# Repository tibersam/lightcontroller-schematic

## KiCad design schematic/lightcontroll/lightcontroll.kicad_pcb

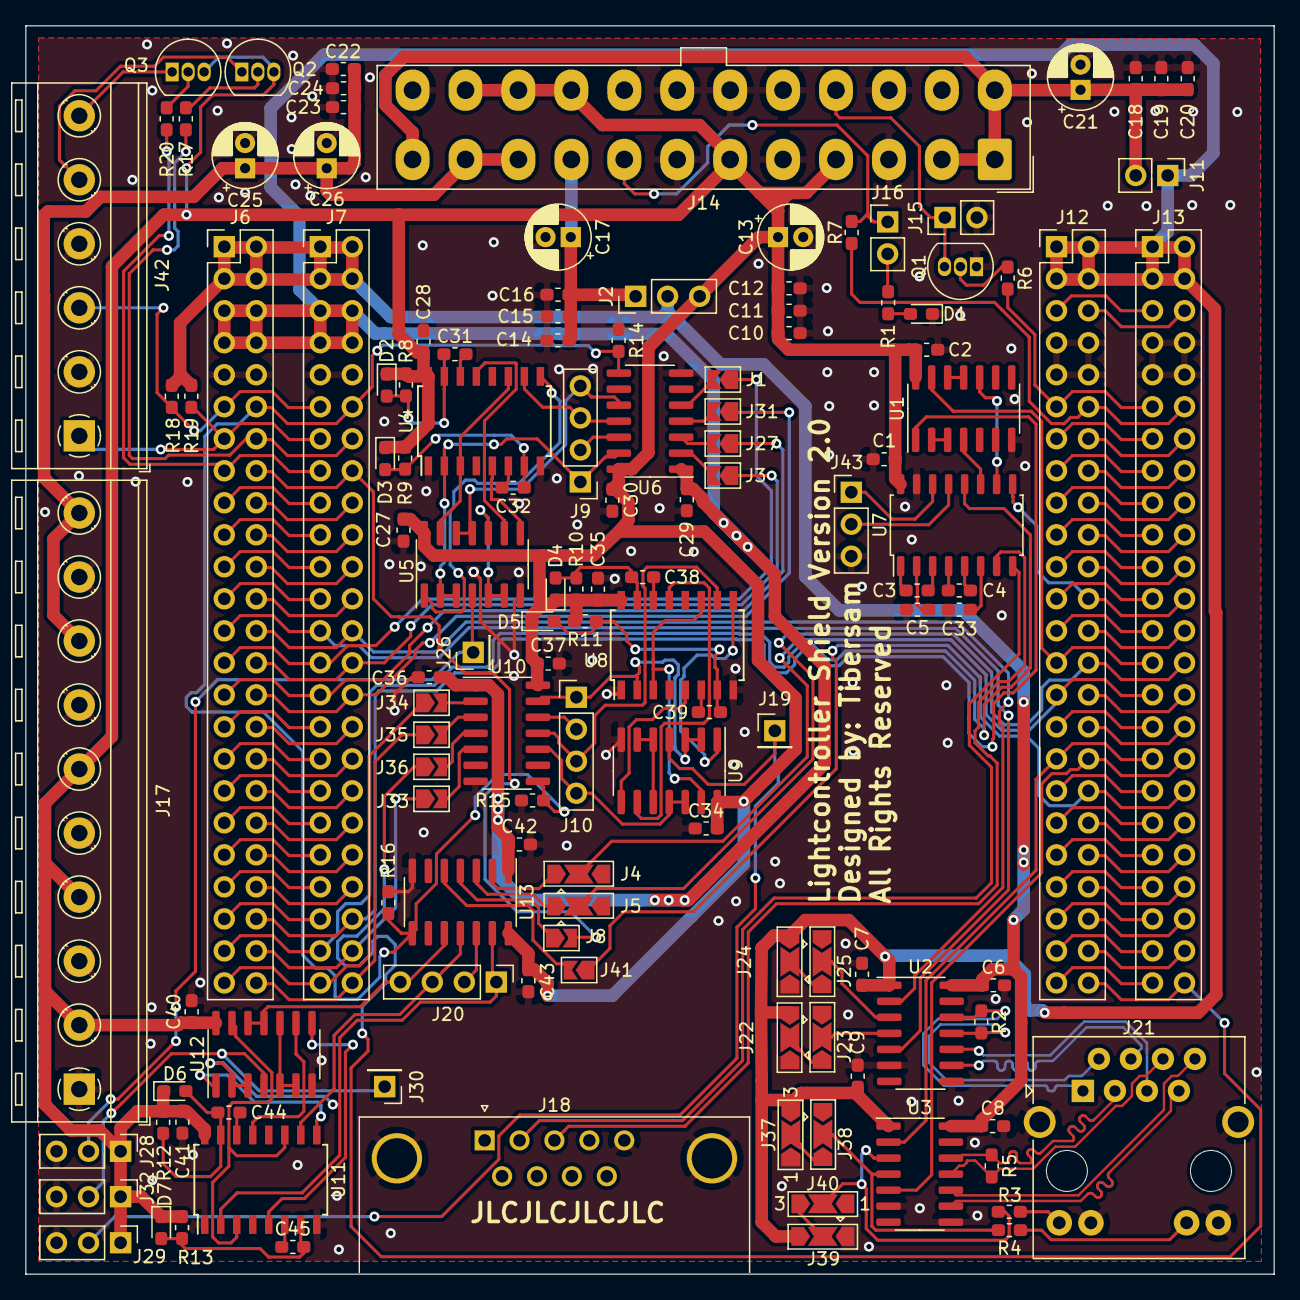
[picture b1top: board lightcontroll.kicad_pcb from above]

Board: 2 copper layers, 99.1 x 99.1 mm, 131 parts (0 on the bottom side), 180 nets.

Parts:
C1, C3, C4, C5, C6, C8, C11, C15, C19, C23, C33: 1uF; C_0603_1608Metric_Pad1.05x0.95mm_HandSolder
C2, C7, C9, C10, C14, C18, C22, C27, C28, C29, C30, C34, C35, C36, C37, C40, C41, C42, C43: 100nF; C_0603_1608Metric_Pad1.05x0.95mm_HandSolder
C12, C16, C20, C24: 10uF; C_0603_1608Metric_Pad1.05x0.95mm_HandSolder
C13, C17, C21, C25, C26: 100uF; CP_Radial_D5.0mm_P2.00mm
C31, C32, C38, C39, C44, C45: 200pF; C_0603_1608Metric_Pad1.05x0.95mm_HandSolder
D1: LED; LED_0603_1608Metric_Pad1.05x0.95mm_HandSolder
D2, D3, D4, D5, D6, D7: D_Schottky; D_0603_1608Metric_Pad1.05x0.95mm_HandSolder
J1: SPI1_SS; SolderJumper-2_P1.3mm_Open_TrianglePad1.0x1.5mm
J2: 5V Selector; PinHeader_1x03_P2.54mm_Vertical
J3: SPI1_CLK; SolderJumper-2_P1.3mm_Open_TrianglePad1.0x1.5mm
J4, J5: UART/SPI JUMPER; SolderJumper-3_P2.0mm_Open_TrianglePad1.0x1.5mm
J6, J7: Conn_02x24_Odd_Even; PinHeader_2x24_P2.54mm_Vertical
J8: UART/SPI JUMPER; SolderJumper-2_P1.3mm_Open_TrianglePad1.0x1.5mm
J9, J10, J20: SPI 5V; PinHeader_1x04_P2.54mm_Vertical
J11: 3.3V jumper; PinHeader_1x02_P2.54mm_Vertical
J12, J13: Header 24X2; PinHeader_2x24_P2.54mm_Vertical
J14: ATX24connector; Molex_Mini-Fit_Jr_5566-24A_2x12_P4.20mm_Vertical
J15, J16: PWR_JMP; PinHeader_1x02_P2.54mm_Vertical
J17: Power Connector; TerminalBlock_RND_205-00295_1x10_P5.08mm_Horizontal
J18: DB9_Female_MountingHoles; DSUB-9_Male_Horizontal_P2.77x2.84mm_EdgePinOffset7.70mm_Hou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
J19, J26, J30: SK2812_sig; PinHeader_1x01_P2.54mm_Vertical
J21: RJ45_LED_Shielded; RJ45_BEL_SS74301-00x_Vertical
J22, J23, J24, J25, J38, J39: Conn_01x03; SolderJumper-3_P2.0mm_Open_TrianglePad1.0x1.5mm
J27: SPI1_MISO; SolderJumper-2_P1.3mm_Open_TrianglePad1.0x1.5mm
J28, J29, J32, J43: Conn_01x03; PinHeader_1x03_P2.54mm_Vertical
J31: SPI1_MOSI; SolderJumper-2_P1.3mm_Open_TrianglePad1.0x1.5mm
J33: SPI2_SS; SolderJumper-2_P1.3mm_Open_TrianglePad1.0x1.5mm
J34: SPI2_CLK; SolderJumper-2_P1.3mm_Open_TrianglePad1.0x1.5mm
J35: SPI2_MISO; SolderJumper-2_P1.3mm_Open_TrianglePad1.0x1.5mm
J36: SPI2_MOSI; SolderJumper-2_P1.3mm_Open_TrianglePad1.0x1.5mm
J37, J40: Conn_01x03; SolderJumper-3_P2.0mm_Open_TrianglePad1.0x1.5mm_NumberLabels
J41: Conn_01x02; SolderJumper-2_P1.3mm_Open_TrianglePad1.0x1.5mm
J42: Buttonconnector; TerminalBlock_RND_205-00291_1x06_P5.08mm_Horizontal
Q1: 2N7000; TO-92_Inline
Q2, Q3: 2N2222A; TO-92_Inline
R1, R3, R4: 200; R_0603_1608Metric_Pad1.05x0.95mm_HandSolder
R2, R5: 120; R_0603_1608Metric_Pad1.05x0.95mm_HandSolder
R6, R7: 10K; R_0603_1608Metric_Pad1.05x0.95mm_HandSolder
R8, R10, R12: 6.5k; R_0603_1608Metric_Pad1.05x0.95mm_HandSolder
R9, R11, R13: 3.3K; R_0603_1608Metric_Pad1.05x0.95mm_HandSolder
R14, R15, R16: 100k; R_0603_1608Metric_Pad1.05x0.95mm_HandSolder
R17, R20: 1K; R_0603_1608Metric_Pad1.05x0.95mm_HandSolder
R18, R19: 100K; R_0603_1608Metric_Pad1.05x0.95mm_HandSolder
U1: 74HC14; SOIC-14_3.9x8.7mm_P1.27mm
U2, U3: MAX13433EESD; SOIC-14_3.9x8.7mm_P1.27mm
U4, U8, U11: 74LS123; SOIC-16W_5.3x10.2mm_P1.27mm
U5, U9, U12: 7402; SOIC-14_3.9x8.7mm_P1.27mm
U6, U10, U13: TXB0104D; SOIC-14_3.9x8.7mm_P1.27mm
U7: MAX232; SOP-16_4.55x10.3mm_P1.27mm

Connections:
+3V3: C18.1, C19.1, C20.1, C21.1, J11.2, J14.1, J14.2, J14.12, J14.13
+5VD: C1.1, C2.1, C10.1, C11.1, C12.1, C13.1, C27.1, C28.1, C30.2, C34.1, C35.1, C37.2, C40.1, C41.1, C43.2, D2.1, D3.1, D4.1, D5.1, D6.1, D7.1, J2.3, J14.4, J14.6, J14.21, J14.22, J14.23, J17.2, J17.4, J17.6, J28.1, J29.1, J32.1, Q2.3, Q3.3, R8.1, R9.1, R10.1, R11.1, R12.1, R13.1, U1.14, U4.16, U5.14, U6.14, U7.16, U8.16, U9.14, U10.14, U11.16, U12.14, U13.14
+5VL: C14.1, C15.1, C16.1, C17.1, J2.1, J14.9
+12V: C22.1, C23.1, C24.1, C25.1, C26.1, J14.10, J14.11, J17.8, J17.10
/3V3_MC: C7.1, C9.1, C29.1, C36.1, C42.1, J6.5, J6.6, J6.7, J6.8, J7.5, J7.6, J7.7, J7.8, J11.1, J12.1, J12.2, J12.3, J12.4, J13.1, J13.2, J13.3, J13.4, J22.3, J24.3, J37.3, J39.3, U2.1, U3.1, U6.1, U10.1, U13.1
/5V_UART: C6.1, C8.1, J2.2, J6.1, J6.2, J6.3, J6.4, J7.1, J7.2, J7.3, J7.4, R18.2, R19.1, U2.14, U3.14
/ATX_Power/PS_ON: J14.16, J15.1, Q1.3
/ATX_Power/PWR_OK_INT: J14.8, J16.1, R7.2
/En_Level_SPI: J6.12, J7.12, R14.2, R15.2, R16.2, U6.8, U10.8, U13.8
/PE2: J6.11, J7.11, J42.3, R19.2
/PE4: J6.13, J7.13, J42.1, R18.1
/PE5: J6.14, J7.14, R17.2
/PE6: J6.15, J7.15, R20.2
/PS_ON: J12.11, J13.11, R6.2
/PWR_OK: J12.12, J13.12, R7.1
/SPI1_CLK: J3.2, U6.2
/SPI1_MISO: J27.2, U6.3
/SPI1_MOSI: J31.2, U6.4
/SPI1_SS: J1.2, U6.5
/SPI2_CLK: J34.2, U10.2
/SPI2_MISO: J35.2, U10.3
/SPI2_MOSI: J36.2, U10.4
/SPI2_SS: J33.2, U10.5
/SPI3_CLK: J4.1, U13.2
/SPI3_MISO: J5.1, U13.3
/SPI3_MOSI: J8.1, U13.4
/SPI3_SS: J41.2, U13.5
/SPI_WS2812_DRIVERS/CLK5V: J9.1, U4.2, U5.2, U5.3, U6.13
/SPI_WS2812_DRIVERS/CLR: U4.3, U4.11, U5.13
/SPI_WS2812_DRIVERS/CS0_5V: J9.4, U5.11, U5.12, U6.10
/SPI_WS2812_DRIVERS/MOSI5V: J9.3, U4.10, U6.11
/SPI_WS2812_DRIVERS/ONE: U4.5, U5.8
/SPI_WS2812_DRIVERS/SK2812_sig: J26.1, J28.2, U5.4
/SPI_WS2812_DRIVERS/Zero: U4.13, U5.9
/UART1_RX: J12.33, J13.33, U3.2
/UART1_TX: J12.34, J13.34, U3.5
/UART2_RX: J6.26, J7.26, U2.2
/UART2_TX: J6.25, J7.25, U2.5
/UART3_RX: J6.45, J7.45, U7.12
/UART3_TX: J6.44, J7.44, U1.1
/UART5_RX: J12.24, J13.24, U7.9
/UART5_TX: J12.27, J13.27, U1.13
/UART6_RX: J12.38, J13.38
/UART6_TX: J12.39, J13.39
/UART Connections/UARTA_RX_EN_JMP: J38.2, R4.1, U3.4
/UART Connections/UARTA_RX_N: J21.6, R5.2, U3.11
/UART Connections/UARTA_RX_P: J21.3, R5.1, U3.12
/UART Connections/UARTA_RX_Voltage: J37.2, J38.3
/UART Connections/UARTA_TX_EN_JMP: J40.2, R3.1, U3.3
/UART Connections/UARTA_TX_N: J21.8, U3.10
/UART Connections/UARTA_TX_P: J21.7, U3.9
/UART Connections/UARTA_TX_Voltage: J39.2, J40.3
/UART Connections/UARTB_RX_EN_JMP: J23.2, U2.4
/UART Connections/UARTB_RX_Voltage: J22.2, J23.3
/UART Connections/UARTB_TX_EN_JMP: J25.2, U2.3
/UART Connections/UARTB_TX_Voltage: J24.2, J25.3
/UART Connections/uartb_rx+: J21.1, R2.1, U2.12
/UART Connections/uartb_rx-: J21.2, R2.2, U2.11
/UART Connections/uartb_tx+: J21.4, U2.9
/UART Connections/uartb_tx-: J21.5, U2.10
/UART_RS232/UARTA_RS232_TX: U1.4, U7.11
/UART_RS232/UARTB_RS232_TX: U1.10, U7.10
/UART_RS232/USARTARX: J43.2, U7.13
/UART_RS232/USARTATX: J43.1, U7.14
/sheet5EBD8EE4/CLK5V: J10.1, U8.2, U9.2, U9.3, U10.13
/sheet5EBD8EE4/CLR: U8.3, U8.11, U9.13
/sheet5EBD8EE4/CS0_5V: J10.4, U9.11, U9.12, U10.10
/sheet5EBD8EE4/MOSI5V: J10.3, U8.10, U10.11
/sheet5EBD8EE4/ONE: U8.5, U9.8
/sheet5EBD8EE4/SK2812_sig: J19.1, J29.2, U9.4
/sheet5EBD8EE4/Zero: U8.13, U9.9
/sheet5EBDAB70/CLK5V: J20.1, U11.2, U12.2, U12.3, U13.13
/sheet5EBDAB70/CLR: U11.3, U11.11, U12.13
/sheet5EBDAB70/CS0_5V: J20.4, U12.11, U12.12, U13.10
/sheet5EBDAB70/MOSI5V: J20.3, U11.10, U13.11
/sheet5EBDAB70/ONE: U11.5, U12.8
/sheet5EBDAB70/SK2812_sig: J30.1, J32.2, U12.4
/sheet5EBDAB70/Zero: U11.13, U12.9
/stm32f407_blackboard/BOOT1: J12.6, J13.6
/stm32f407_blackboard/Boot0: J12.5, J13.5
/stm32f407_blackboard/PA0,WK_UP: J6.23, J7.23
/stm32f407_blackboard/PA1: J6.24, J7.24
/stm32f407_blackboard/PA4: J1.1, J6.27, J7.27
/stm32f407_blackboard/PA5: J3.1, J6.28, J7.28
/stm32f407_blackboard/PA6: J6.29, J7.29, J27.1
/stm32f407_blackboard/PA7: J6.30, J7.30, J31.1
/stm32f407_blackboard/PA8: J12.35, J13.35
/stm32f407_blackboard/PA11_USB_DM: J12.32, J13.32
/stm32f407_blackboard/PA12USB_DP: J12.31, J13.31
/stm32f407_blackboard/PA15_TD1SWD: J12.30, J13.30
/stm32f407_blackboard/PB0: J6.33, J7.33
/stm32f407_blackboard/PB1: J6.34, J7.34
/stm32f407_blackboard/PB3_TD0_SWD: J12.18, J13.18
/stm32f407_blackboard/PB5: J12.17, J13.17
/stm32f407_blackboard/PB6: J12.16, J13.16
/stm32f407_blackboard/PB7: J12.15, J13.15
/stm32f407_blackboard/PB8: J12.14, J13.14
/stm32f407_blackboard/PB9: J12.13, J13.13
/stm32f407_blackboard/PB12: J6.46, J7.46, J33.1
/stm32f407_blackboard/PB13: J6.47, J7.47, J34.1
/stm32f407_blackboard/PB14: J6.48, J7.48, J35.1
/stm32f407_blackboard/PB15: J12.48, J13.48, J36.1
/stm32f407_blackboard/PC0: J6.17, J7.17
/stm32f407_blackboard/PC1: J6.18, J7.18
/stm32f407_blackboard/PC2: J6.19, J7.19
/stm32f407_blackboard/PC3: J6.20, J7.20
/stm32f407_blackboard/PC4: J6.31, J7.31
/stm32f407_blackboard/PC5: J6.32, J7.32
/stm32f407_blackboard/PC8: J12.37, J13.37
/stm32f407_blackboard/PC9: J12.36, J13.36, J41.1
/stm32f407_blackboard/PC10: J4.2, J12.29, J13.29
/stm32f407_blackboard/PC11: J5.2, J12.28, J13.28
/stm32f407_blackboard/PC13: J6.16, J7.16, J8.2
/stm32f407_blackboard/PD0: J12.26, J13.26
/stm32f407_blackboard/PD1: J12.25, J13.25
/stm32f407_blackboard/PD3: J12.23, J13.23
/stm32f407_blackboard/PD4: J12.22, J13.22
/stm32f407_blackboard/PD5: J12.21, J13.21
/stm32f407_blackboard/PD6: J12.20, J13.20
/stm32f407_blackboard/PD7: J12.19, J13.19
/stm32f407_blackboard/PD8: J12.47, J13.47
/stm32f407_blackboard/PD9: J12.46, J13.46
/stm32f407_blackboard/PD10: J12.45, J13.45
/stm32f407_blackboard/PD11: J12.44, J13.44
/stm32f407_blackboard/PD12: J12.43, J13.43
/stm32f407_blackboard/PD13: J12.42, J13.42
/stm32f407_blackboard/PD14: J12.41, J13.41
/stm32f407_blackboard/PD15: J12.40, J13.40
/stm32f407_blackboard/PE7: J6.35, J7.35
/stm32f407_blackboard/PE8: J6.36, J7.36
/stm32f407_blackboard/PE9: J6.37, J7.37
/stm32f407_blackboard/PE10: J6.38, J7.38
/stm32f407_blackboard/PE11: J6.39, J7.39
/stm32f407_blackboard/PE12: J6.40, J7.40
/stm32f407_blackboard/PE13: J6.41, J7.41
/stm32f407_blackboard/PE14: J6.42, J7.42
/stm32f407_blackboard/PE15: J6.43, J7.43
/stm32f407_blackboard/VREF+: J6.22, J7.22
/stm32f407_blackboard/VREF-: J6.21, J7.21
GNDREF: C1.2, C2.2, C5.2, C6.2, C7.2, C8.2, C9.2, C10.2, C11.2, C12.2, C13.2, C14.2, C15.2, C16.2, C17.2, C18.2, C19.2, C20.2, C21.2, C22.2, C23.2, C24.2, C25.2, C26.2, C27.2, C28.2, C29.2, C30.1, C33.1, C34.2, C35.2, C36.2, C37.1, C40.2, C41.2, C42.2, C43.1, D1.1, J6.9, J6.10, J7.9, J7.10, J12.7, J12.8, J12.9, J12.10, J13.7, J13.8, J13.9, J13.10, J14.3, J14.5, J14.7, J14.15, J14.17, J14.18, J14.19, J14.24, J15.2, J17.1, J17.3, J17.5, J17.7, J17.9, J18.0, J18.5, J21.9, J21.11, J21.SH, J22.1, J24.1, J28.3, J29.3, J32.3, J37.1, J39.1, J42.2, J42.4, J43.3, Q1.1, R14.1, R15.1, R16.1, U1.7, U2.6, U2.8, U3.6, U3.8, U4.1, U4.8, U5.7, U6.7, U7.15, U8.1, U8.8, U9.7, U10.7, U11.1, U11.8, U12.7, U13.7
unnamed: C3.1, U7.1
unnamed: C3.2, U7.3
unnamed: C4.1, U7.4
unnamed: C4.2, U7.5
unnamed: C5.1, U7.2
unnamed: C31.1, D2.2, R8.2, U4.15
unnamed: C31.2, U4.14
unnamed: C32.1, U4.6
unnamed: C32.2, D3.2, R9.2, U4.7
unnamed: C33.2, U7.6
unnamed: C38.1, D4.2, R10.2, U8.15
unnamed: C38.2, U8.14
unnamed: C39.1, U8.6
unnamed: C39.2, D5.2, R11.2, U8.7
unnamed: C44.1, D6.2, R12.2, U11.15
unnamed: C44.2, U11.14
unnamed: C45.1, U11.6
unnamed: C45.2, D7.2, R13.2, U11.7
unnamed: D1.2, R1.2
unnamed: J9.2, U6.12
unnamed: J10.2, U10.12
unnamed: J16.2, R1.1
unnamed: J18.2, U7.8
unnamed: J18.3, U7.7
unnamed: J20.2, U13.12
unnamed: J21.10, R4.2
unnamed: J21.12, R3.2
unnamed: J42.5, Q2.1
unnamed: J42.6, Q3.1
unnamed: Q1.2, R6.1
unnamed: Q2.2, R17.1
unnamed: Q3.2, R20.1
unnamed: U1.2, U1.3
unnamed: U1.11, U1.12
unnamed: U4.9, U5.1
unnamed: U5.5, U5.6, U5.10
unnamed: U8.9, U9.1
unnamed: U9.5, U9.6, U9.10
unnamed: U11.9, U12.1
unnamed: U12.5, U12.6, U12.10

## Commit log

2019-03-19 save before potential crash
2019-03-23 build backup
2019-04-03 save state
2020-05-26 Update backup of circuit
2020-09-10 save Version 1.0
2021-04-10 save current state of project. Added gitignore for kicad
2022-01-22 Updated PCB to Revision 2.0
    - Added an 2.54mm pin header for second RS232 UART, which was already available in rev 1.0
    - Changed all 2.00mm pin header to 2.54mm pin header. This fixes the mistake done in selecting the wrong footprint in rev 1.0
    - Corrected schematic and layout of the spi to sk2812 circuits. During testing of previous rev some mistakes where found.
    * the second logical schemitac part of 74ls123 changes meaning of pin 6 and 7 compared to 15 and 14 of the first
    * The vibrator for the one signal needs to be also triggered with every rising edge, so use input A instead of binding it to gnd
    * Use the fourth nand to invert clock signal for a input of one vibrator
2022-01-22 added zip archive to restore project back to this state if need be.

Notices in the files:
schematic/lightcontroll/lightcontroll.kicad_pcb:
All Rights Reserved
